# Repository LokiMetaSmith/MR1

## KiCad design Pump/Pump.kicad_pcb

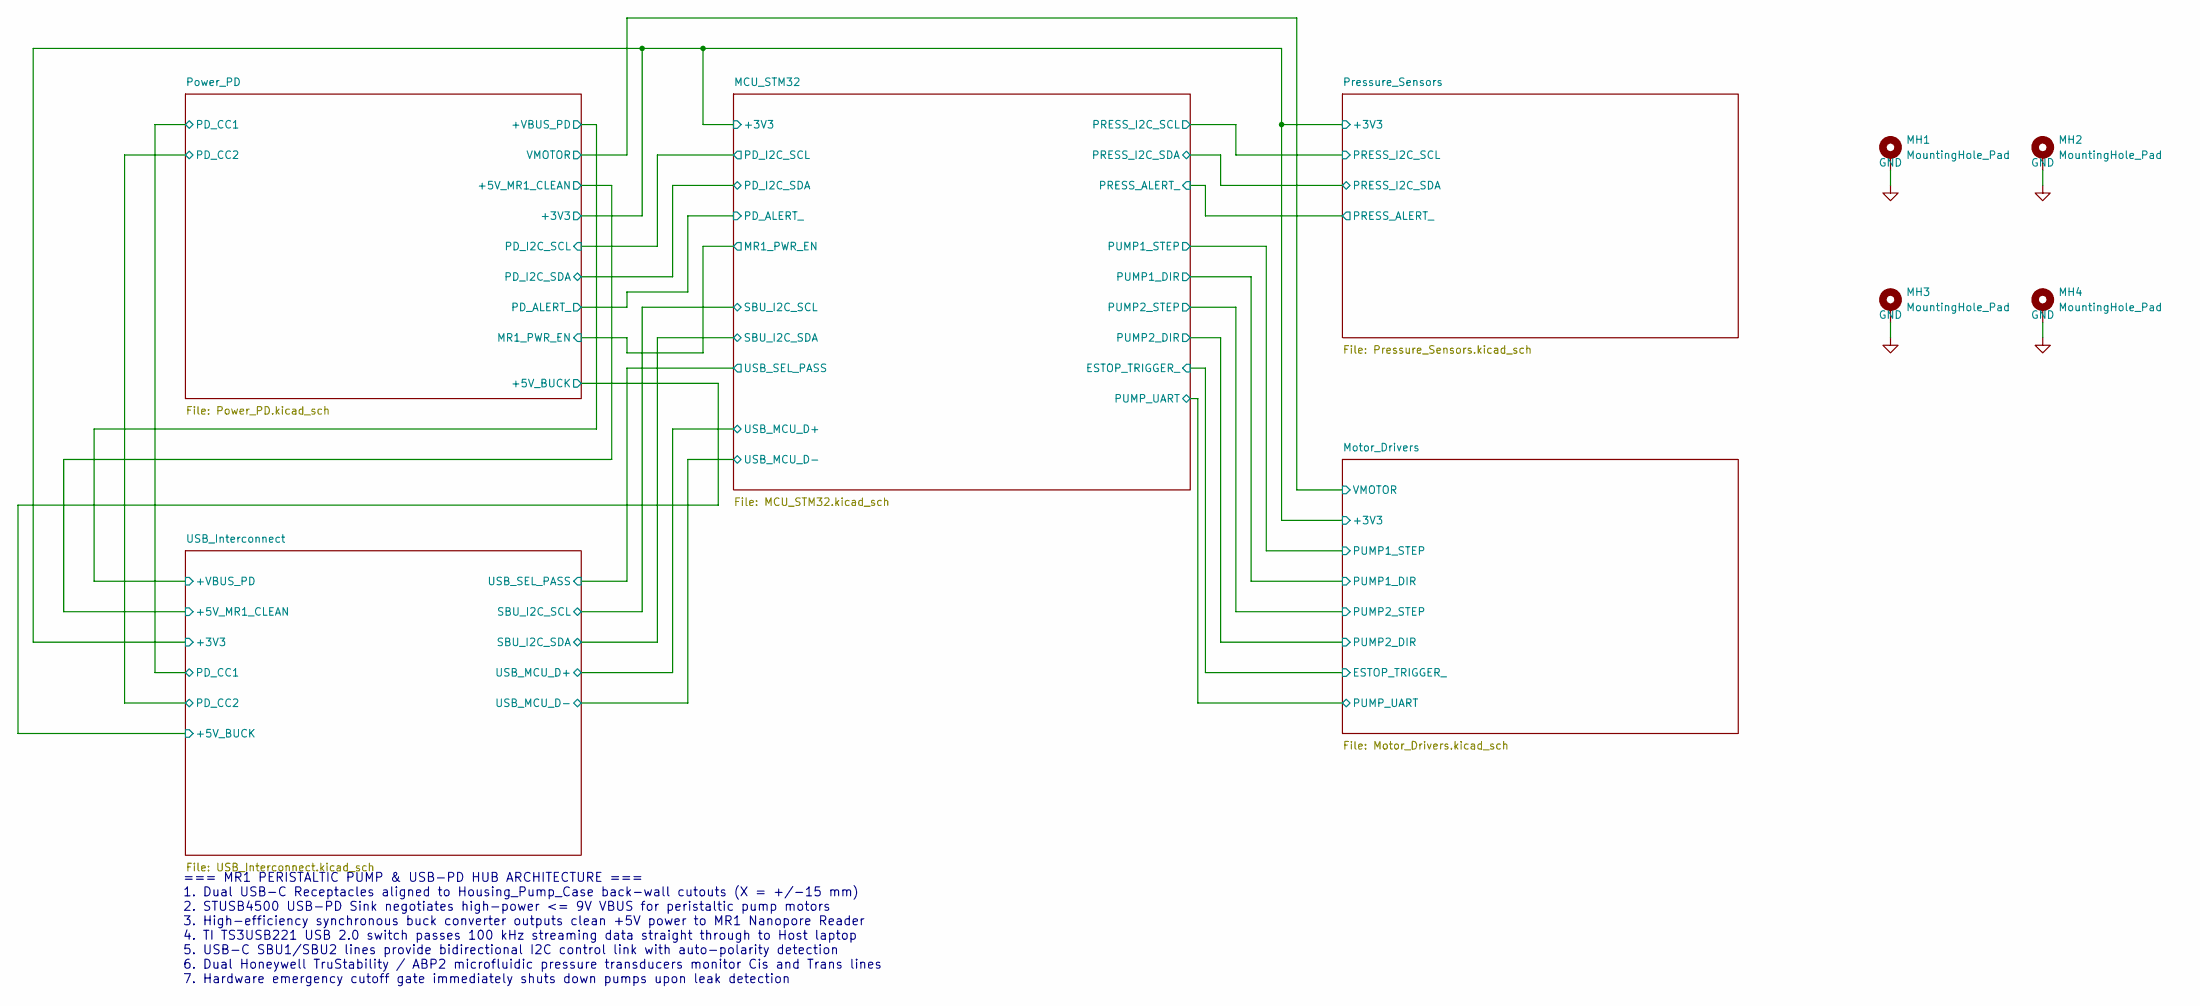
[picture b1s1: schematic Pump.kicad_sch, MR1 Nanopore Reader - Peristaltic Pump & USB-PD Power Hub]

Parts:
MH1, MH2, MH3, MH4: MountingHole_Pad; MountingHole_3.2mm_M3_Pad

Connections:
GND: MH1.1, MH2.1, MH3.1, MH4.1; also elsewhere on the board

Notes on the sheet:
=== MR1 PERISTALTIC PUMP & USB-PD HUB ARCHITECTURE === 1. Dual USB-C Receptacles aligned to Housing_Pump_Case back-wall cutouts (X = +/-15 mm) 2. STUSB4500 USB-PD Sink negotiates high-power <= 9V VBUS for peristaltic pump motors 3. High-efficiency synchronous buck converter outputs clean +5V power 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

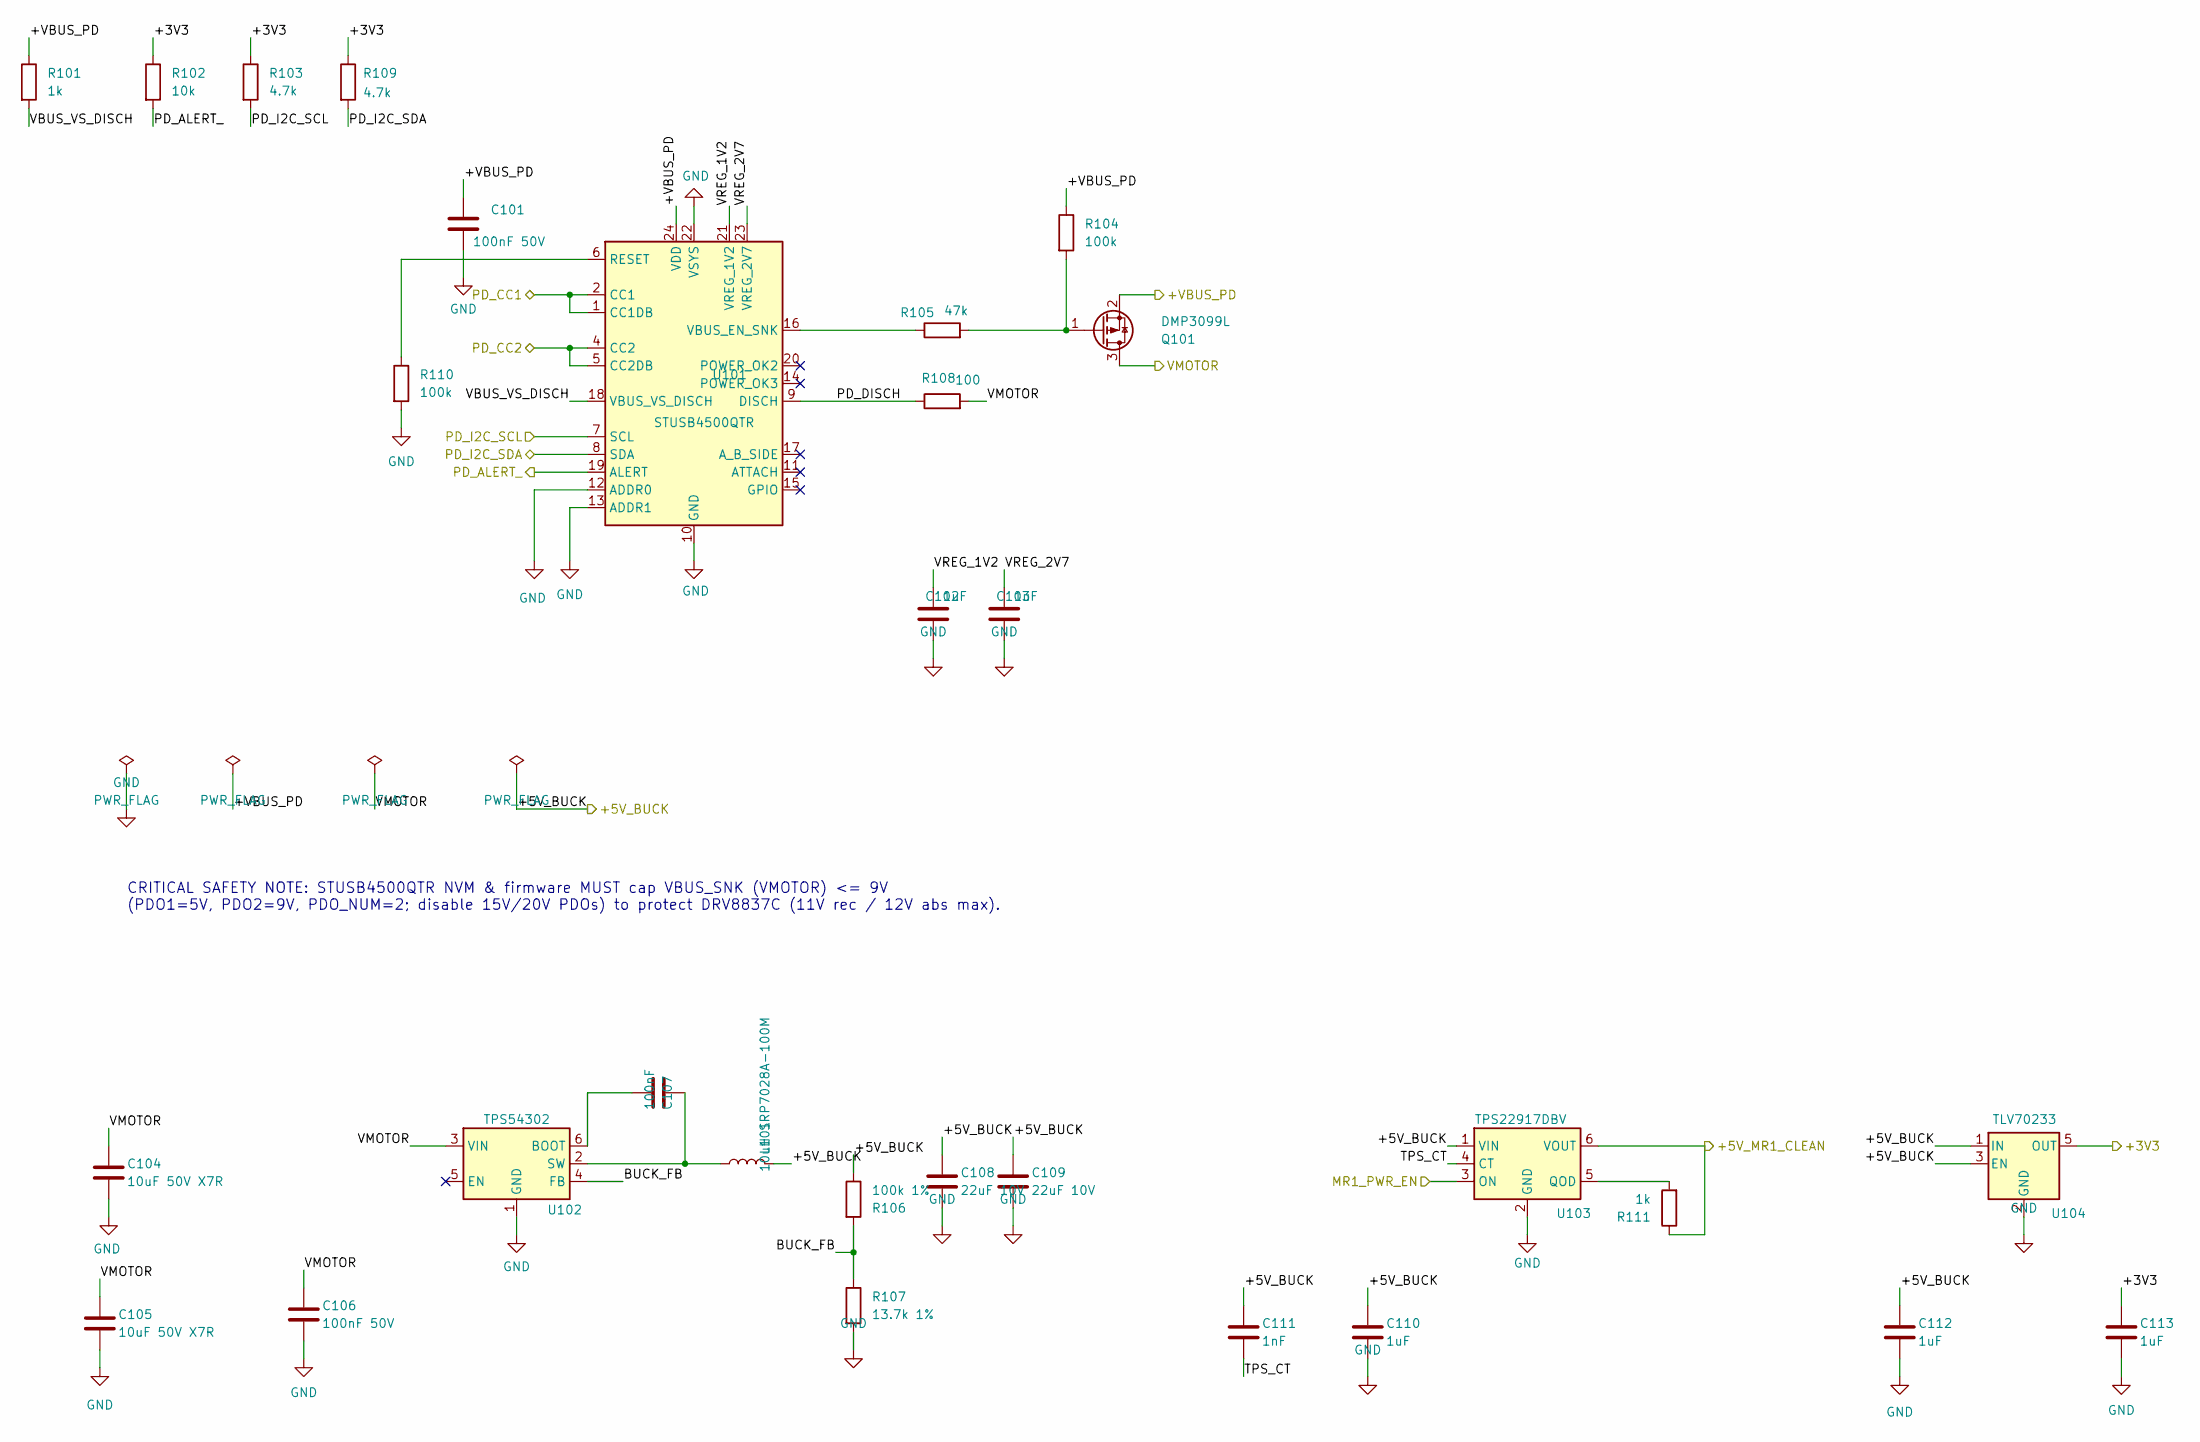
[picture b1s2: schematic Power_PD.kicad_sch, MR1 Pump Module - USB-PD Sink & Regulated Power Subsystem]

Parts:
C101, C106: 100nF 50V; C_0603_1608Metric; MPN CL10B104KB8NNNC; LCSC C1591
C102, C103, C110, C112, C113: 1uF; C_0402_1005Metric; MPN CL05A105KO5NNNC; LCSC C29266
C104, C105: 10uF 50V X7R; C_1206_3216Metric; MPN CL31B106KBHNNNE; LCSC C89632
C107: 100nF; C_0402_1005Metric; MPN CL05B104KO5NNNC; LCSC C1525
C108, C109: 22uF 10V; C_0805_2012Metric; MPN CL21A226MAQNNNE; LCSC C45783
C111: 1nF; C_0402_1005Metric; MPN 0402B102K500NT; LCSC C1523
L101: 10uH SRP7028A-100M; L_Bourns_SRP7028A_7.3x6.6mm; MPN SRP7028A-100M; LCSC C2687402
Q101: DMP3099L; SOT-23; MPN DMP3099L-7; LCSC C155244
R101, R111: 1k; R_0402_1005Metric; MPN 0402WGF1001TCE; LCSC C11702
R102: 10k; R_0402_1005Metric; MPN RC0402FR-0710KL; LCSC C60490
R103, R109: 4.7k; R_0402_1005Metric; MPN 0402WGF4701TCE; LCSC C25900
R104, R110: 100k; R_0402_1005Metric; MPN RC0402FR-07100KL; LCSC C60491
R105: 47k; R_0402_1005Metric; MPN 0402WGF4702TCE; LCSC C25792
R106: 100k 1%; R_0402_1005Metric; MPN RC0402FR-07100KL; LCSC C60491
R107: 13.7k 1%; R_0402_1005Metric; MPN RC0402FR-0713K7L; LCSC C274888
R108: 100; R_0402_1005Metric; MPN 0402WGF1000TCE; LCSC C25076
U101: STUSB4500QTR; QFN-24-1EP_4x4mm_P0.5mm_EP2.7x2.7mm; MPN STUSB4500QTR; LCSC C2678061
U102: TPS54302; SOT-23-6; MPN TPS54302DDCR; LCSC C311983
U103: TPS22917DBV; SOT-23-6; MPN TPS22917DBVR; LCSC C2681320
U104: TLV70233; SOT-23-5; MPN TLV70233DBVR; LCSC C26833

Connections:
/MCU_STM32/+3V3: C113.1, R102.1, R103.1, R109.1, U104.5 (OUT); also elsewhere on the board
/MCU_STM32/MR1_PWR_EN: U103.3 (ON); also elsewhere on the board
/Motor_Drivers/VMOTOR: C104.1, C105.1, C106.1, Q101.3 (D), R108.2, U102.3 (VIN); also elsewhere on the board
/Power_PD/+5V_BUCK: C108.1, C109.1, C110.1, C111.1, C112.1, L101.2, R106.1, U103.1 (VIN), U104.1 (IN), U104.3 (EN); also elsewhere on the board
/Power_PD/+VBUS_PD: C101.1, Q101.2 (S), R101.1, R104.1, U101.24 (VDD); also elsewhere on the board
/Power_PD/BUCK_FB: R106.2, R107.1, U102.4 (FB)
/Power_PD/PD_ALERT_: R102.2, U101.19 (ALERT); also elsewhere on the board
/Power_PD/PD_CC1: U101.1 (CC1DB), U101.2 (CC1); also elsewhere on the board
/Power_PD/PD_CC2: U101.4 (CC2), U101.5 (CC2DB); also elsewhere on the board
/Power_PD/PD_DISCH: R108.1, U101.9 (DISCH)
/Power_PD/PD_I2C_SCL: R103.2, U101.7 (SCL); also elsewhere on the board
/Power_PD/PD_I2C_SDA: R109.2, U101.8 (SDA); also elsewhere on the board
/Power_PD/TPS_CT: C111.2, U103.4 (CT)
/Power_PD/VBUS_VS_DISCH: R101.2, U101.18 (VBUS_VS_DISCH)
/Power_PD/VREG_1V2: C102.1, U101.21 (VREG_1V2)
/Power_PD/VREG_2V7: C103.1, U101.23 (VREG_2V7)
/USB_Interconnect/+5V_MR1_CLEAN: R111.1, U103.6 (VOUT); also elsewhere on the board
GND: C101.2, C102.2, C103.2, C104.2, C105.2, C106.2, C108.2, C109.2, C110.2, C112.2, C113.2, R107.2, R110.2, U101.10 (GND), U101.12 (ADDR0), U101.13 (ADDR1), U101.22 (VSYS), U101.25 (GND), U102.1 (GND), U103.2 (GND), U104.2 (GND); also elsewhere on the board
unnamed: Q101.1 (G), R104.2, R105.2
unnamed: R110.1, U101.6 (RESET)
unnamed: R105.1, U101.16 (VBUS_EN_SNK)
unnamed: C107.1, U102.6 (BOOT)
unnamed: C107.2, L101.1, U102.2 (SW)
unnamed: R111.2, U103.5 (QOD)

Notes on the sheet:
CRITICAL SAFETY NOTE: STUSB4500QTR NVM & firmware MUST cap VBUS_SNK (VMOTOR) <= 9V (PDO1=5V, PDO2=9V, PDO_NUM=2; disable 15V/20V PDOs) to protect DRV8837C (11V rec / 12V abs max).

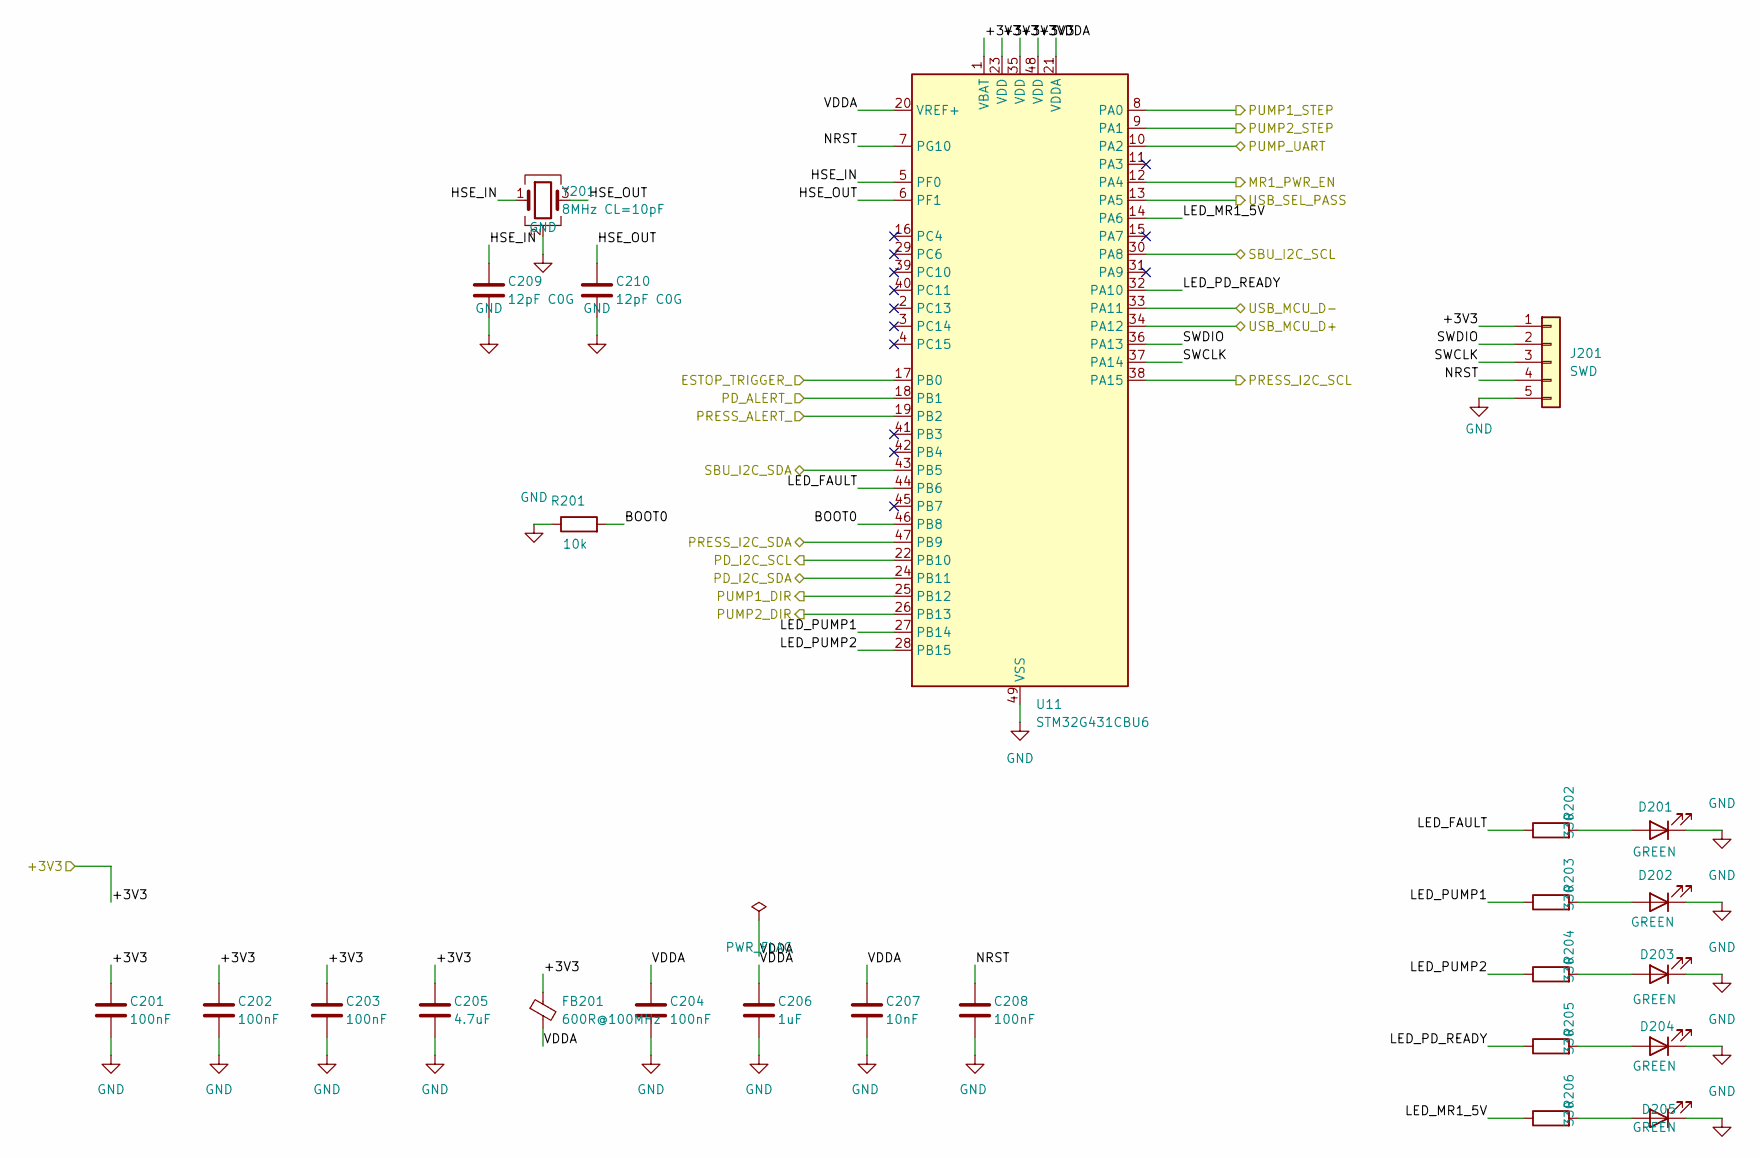
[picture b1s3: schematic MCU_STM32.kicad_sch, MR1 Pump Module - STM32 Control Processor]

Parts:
C201, C202, C203, C204, C208: 100nF; C_0402_1005Metric; MPN CL05B104KO5NNNC; LCSC C1525
C205: 4.7uF; C_0603_1608Metric; MPN CL10A475KP8NNNC; LCSC C1705
C206: 1uF; C_0402_1005Metric; MPN CL05A105KO5NNNC; LCSC C29266
C207: 10nF; C_0402_1005Metric; MPN CL05B103KB5NNNC; LCSC C15195
C209, C210: 12pF C0G; C_0402_1005Metric; MPN 0402CG120J500NT; LCSC C1547
D201, D202, D203, D204, D205: GREEN; LED_0603_1608Metric; MPN KT-0603G; LCSC C12624
FB201: 600R@100MHz; L_0603_1608Metric; MPN CBW160808U601T; LCSC C139183
J201: SWD; PinHeader_1x05_P2.54mm_Vertical; MPN PZ254V-11-05P; LCSC C492404
R201: 10k; R_0402_1005Metric; MPN RC0402FR-0710KL; LCSC C60490
R202, R203, R204, R205, R206: 330; R_0402_1005Metric; MPN 0402WGF3300TCE; LCSC C25104
U11: STM32G431CBU6; QFN-48-1EP_7x7mm_P0.5mm_EP5.6x5.6mm; MPN STM32G431CBU6; LCSC C529356
Y201: 8MHz CL=10pF; Crystal_SMD_3225-4Pin_3.2x2.5mm; MPN 3225-8.00-10-10-10/A; LCSC C518154

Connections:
/MCU_STM32/+3V3: C201.1, C202.1, C203.1, C205.1, FB201.1, J201.1, U11.1 (VBAT), U11.23 (VDD), U11.35 (VDD), U11.48 (VDD); also elsewhere on the board
/MCU_STM32/BOOT0: R201.2, U11.46 (PB8)
/MCU_STM32/ESTOP_TRIGGER_: U11.17 (PB0); also elsewhere on the board
/MCU_STM32/HSE_IN: C209.1, U11.5 (PF0), Y201.1
/MCU_STM32/HSE_OUT: C210.1, U11.6 (PF1), Y201.3
/MCU_STM32/LED_FAULT: R202.1, U11.44 (PB6)
/MCU_STM32/LED_MR1_5V: R206.1, U11.14 (PA6)
/MCU_STM32/LED_PD_READY: R205.1, U11.32 (PA10)
/MCU_STM32/LED_PUMP1: R203.1, U11.27 (PB14)
/MCU_STM32/LED_PUMP2: R204.1, U11.28 (PB15)
/MCU_STM32/MR1_PWR_EN: U11.12 (PA4); also elsewhere on the board
/MCU_STM32/NRST: C208.1, J201.4, U11.7 (PG10)
/MCU_STM32/PRESS_ALERT_: U11.19 (PB2); also elsewhere on the board
/MCU_STM32/PUMP1_DIR: U11.25 (PB12); also elsewhere on the board
/MCU_STM32/PUMP1_STEP: U11.8 (PA0); also elsewhere on the board
/MCU_STM32/PUMP2_DIR: U11.26 (PB13); also elsewhere on the board
/MCU_STM32/PUMP2_STEP: U11.9 (PA1); also elsewhere on the board
/MCU_STM32/PUMP_UART: U11.10 (PA2); also elsewhere on the board
/MCU_STM32/SWCLK: J201.3, U11.37 (PA14)
/MCU_STM32/SWDIO: J201.2, U11.36 (PA13)
/MCU_STM32/USB_MCU_D+: U11.34 (PA12); also elsewhere on the board
/MCU_STM32/USB_MCU_D-: U11.33 (PA11); also elsewhere on the board
/MCU_STM32/USB_SEL_PASS: U11.13 (PA5); also elsewhere on the board
/MCU_STM32/VDDA: C204.1, C206.1, C207.1, FB201.2, U11.20 (VREF+), U11.21 (VDDA)
/Power_PD/PD_ALERT_: U11.18 (PB1); also elsewhere on the board
/Power_PD/PD_I2C_SCL: U11.22 (PB10); also elsewhere on the board
/Power_PD/PD_I2C_SDA: U11.24 (PB11); also elsewhere on the board
/Pressure_Sensors/PRESS_I2C_SCL: U11.38 (PA15); also elsewhere on the board
/Pressure_Sensors/PRESS_I2C_SDA: U11.47 (PB9); also elsewhere on the board
/USB_Interconnect/SBU_I2C_SCL: U11.30 (PA8); also elsewhere on the board
/USB_Interconnect/SBU_I2C_SDA: U11.43 (PB5); also elsewhere on the board
GND: C201.2, C202.2, C203.2, C204.2, C205.2, C206.2, C207.2, C208.2, C209.2, C210.2, D201.1 (K), D202.1 (K), D203.1 (K), D204.1 (K), D205.1 (K), J201.5, R201.1, U11.49 (VSS), Y201.2 (G), Y201.4 (G); also elsewhere on the board
unnamed: D201.2 (A), R202.2
unnamed: D202.2 (A), R203.2
unnamed: D203.2 (A), R204.2
unnamed: D204.2 (A), R205.2
unnamed: D205.2 (A), R206.2

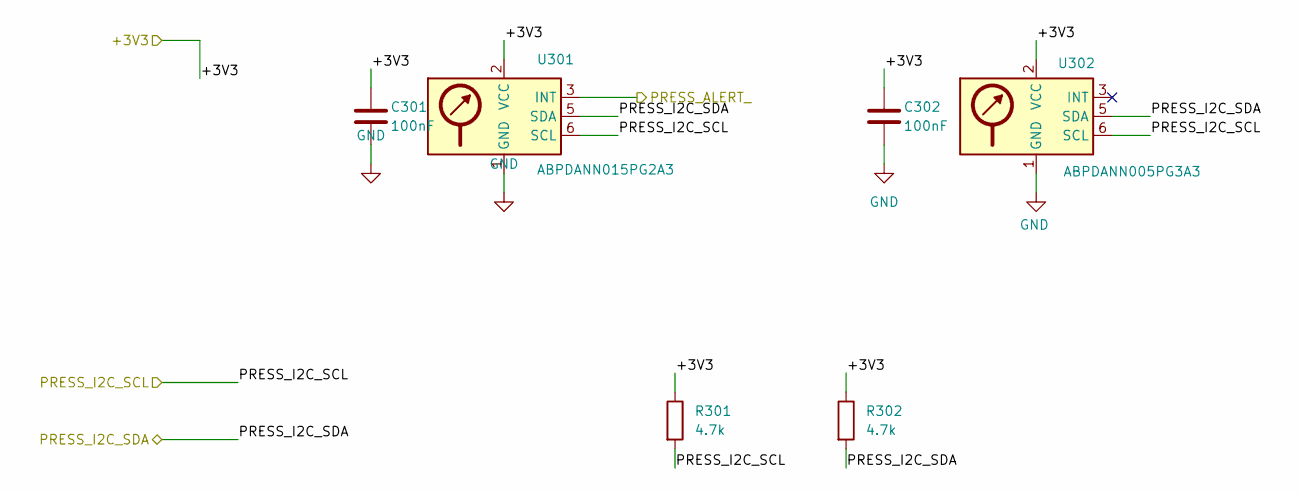
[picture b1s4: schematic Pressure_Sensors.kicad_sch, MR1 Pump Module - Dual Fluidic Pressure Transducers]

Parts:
C301, C302: 100nF; C_0402_1005Metric; MPN CL05B104KO5NNNC; LCSC C1525
R301, R302: 4.7k; R_0402_1005Metric; MPN 0402WGF4701TCE; LCSC C25900
U301: ABPDANN015PG2A3; Honeywell_ABPDAN; MPN ABPDANN015PG2A3; LCSC ABPDANN015PG2A3
U302: ABPDANN005PG3A3; Honeywell_ABPDAN; MPN ABPDANN005PG3A3; LCSC ABPDANN005PG3A3

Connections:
/MCU_STM32/+3V3: C301.1, C302.1, R301.1, R302.1, U301.2 (VCC), U302.2 (VCC); also elsewhere on the board
/MCU_STM32/PRESS_ALERT_: U301.3 (INT); also elsewhere on the board
/Pressure_Sensors/PRESS_I2C_SCL: R301.2, U301.6 (SCL), U302.6 (SCL); also elsewhere on the board
/Pressure_Sensors/PRESS_I2C_SDA: R302.2, U301.5 (SDA), U302.5 (SDA); also elsewhere on the board
GND: C301.2, C302.2, U301.1 (GND), U302.1 (GND); also elsewhere on the board

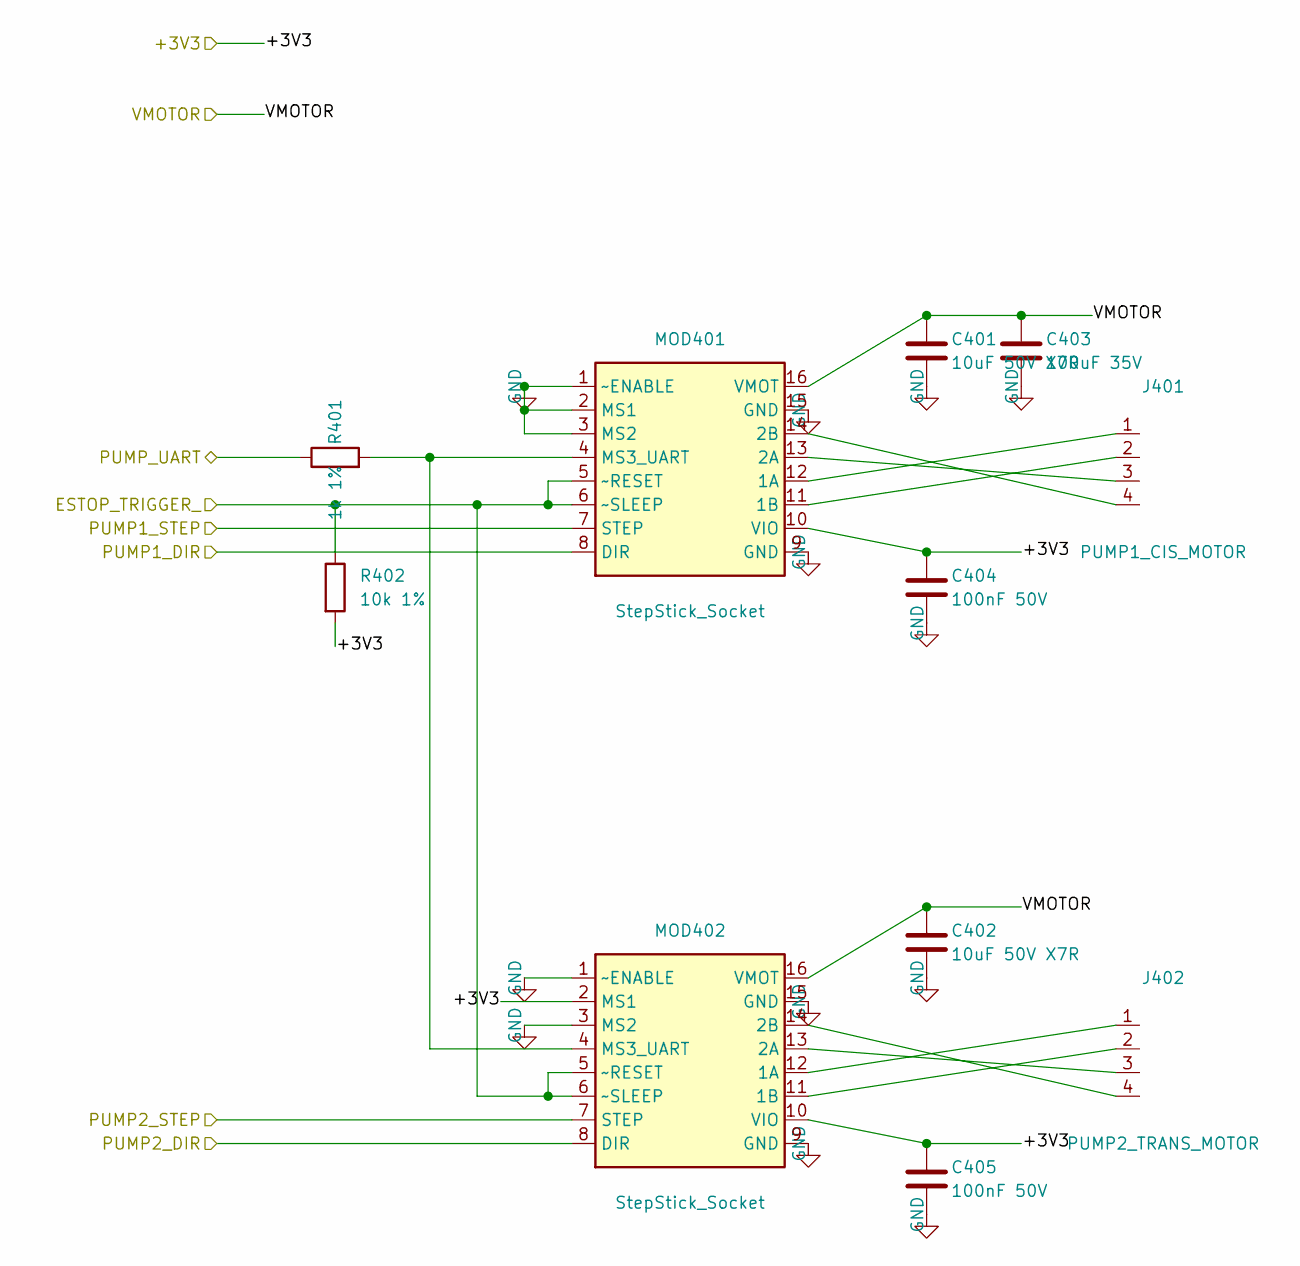
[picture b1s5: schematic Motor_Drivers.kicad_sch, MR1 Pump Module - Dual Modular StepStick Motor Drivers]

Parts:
C401, C402: 10uF 50V X7R; C_1206_3216Metric; MPN CL31B106KBHNNNE; LCSC C89632
C403: 100uF 35V; CP_Elec_6.3x7.7; MPN VT1V101M0607; LCSC C134544
C404, C405: 100nF 50V; C_0402_1005Metric; MPN CL05B104KO5NNNC; LCSC C1525
J401: PUMP1_CIS_MOTOR; JST_XH_B4B-XH-A_1x04_P2.50mm_Vertical; MPN B4B-XH-A(LF)(SN); LCSC C144395
J402: PUMP2_TRANS_MOTOR; JST_XH_B4B-XH-A_1x04_P2.50mm_Vertical; MPN B4B-XH-A(LF)(SN); LCSC C144395
MOD401, MOD402: StepStick_Socket; Pololu_Breakout-16_15.2x20.3mm; MPN PinHeader_1x08_P2.54mm_Female; LCSC C22550
R401: 1k 1%; R_0402_1005Metric; MPN 0402WGF1001TCE; LCSC C11702
R402: 10k 1%; R_0402_1005Metric; MPN 0402WGF1002TCE; LCSC C25744

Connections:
/MCU_STM32/+3V3: C404.1, C405.1, MOD401.10 (VIO), MOD402.2 (MS1), MOD402.10 (VIO), R402.2; also elsewhere on the board
/MCU_STM32/ESTOP_TRIGGER_: MOD401.5 (~RESET), MOD401.6 (~SLEEP), MOD402.5 (~RESET), MOD402.6 (~SLEEP), R402.1; also elsewhere on the board
/MCU_STM32/PUMP1_DIR: MOD401.8 (DIR); also elsewhere on the board
/MCU_STM32/PUMP1_STEP: MOD401.7 (STEP); also elsewhere on the board
/MCU_STM32/PUMP2_DIR: MOD402.8 (DIR); also elsewhere on the board
/MCU_STM32/PUMP2_STEP: MOD402.7 (STEP); also elsewhere on the board
/MCU_STM32/PUMP_UART: R401.1; also elsewhere on the board
/Motor_Drivers/VMOTOR: C401.1, C402.1, C403.1, MOD401.16 (VMOT), MOD402.16 (VMOT); also elsewhere on the board
GND: C401.2, C402.2, C403.2, C404.2, C405.2, MOD401.1 (~ENABLE), MOD401.2 (MS1), MOD401.3 (MS2), MOD401.9 (GND), MOD401.15 (GND), MOD402.1 (~ENABLE), MOD402.3 (MS2), MOD402.9 (GND), MOD402.15 (GND); also elsewhere on the board
unnamed: J401.1, MOD401.12 (1A)
unnamed: J401.2, MOD401.11 (1B)
unnamed: J401.3, MOD401.13 (2A)
unnamed: J401.4, MOD401.14 (2B)
unnamed: J402.1, MOD402.12 (1A)
unnamed: J402.2, MOD402.11 (1B)
unnamed: J402.3, MOD402.13 (2A)
unnamed: J402.4, MOD402.14 (2B)
unnamed: MOD401.4 (MS3_UART), MOD402.4 (MS3_UART), R401.2

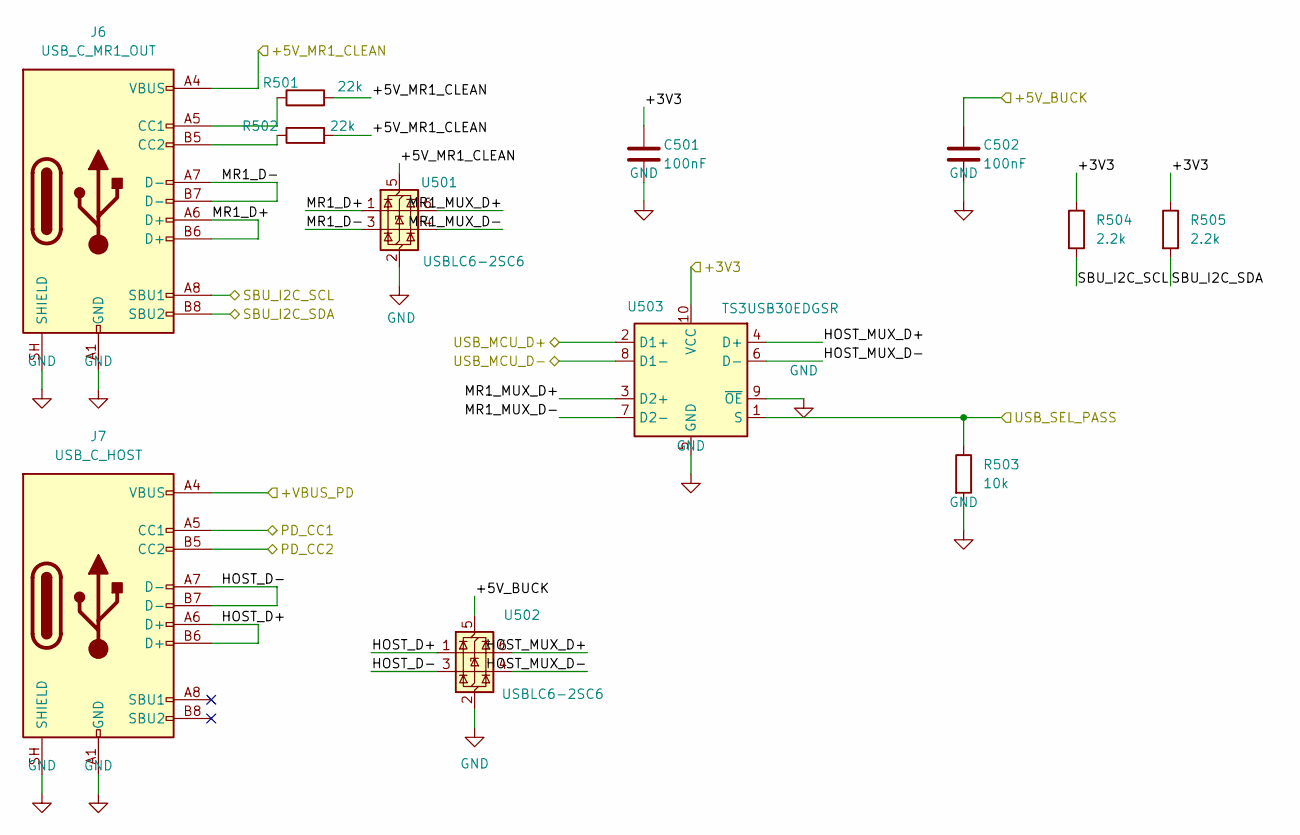
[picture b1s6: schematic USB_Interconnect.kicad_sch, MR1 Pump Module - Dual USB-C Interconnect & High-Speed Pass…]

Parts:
C501, C502: 100nF; C_0402_1005Metric; MPN CL05B104KO5NNNC; LCSC C1525
J6: USB_C_MR1_OUT; USB_C_Receptacle_GCT_USB4085; MPN USB4085-GF-A; LCSC C7095263
J7: USB_C_HOST; USB_C_Receptacle_GCT_USB4085; MPN USB4085-GF-A; LCSC C7095263
R501, R502: 22k; R_0402_1005Metric; MPN 0402WGF2202TCE; LCSC C25768
R503: 10k; R_0402_1005Metric; MPN RC0402FR-0710KL; LCSC C60490
R504, R505: 2.2k; R_0402_1005Metric; MPN 0402WGF2201TCE; LCSC C25879
U501, U502: USBLC6-2SC6; SOT-23-6; MPN USBLC6-2SC6; LCSC C7519
U503: TS3USB30EDGSR; TSSOP-10_3x3mm_P0.5mm; MPN TS3USB30EDGSR; LCSC C131998

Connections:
/MCU_STM32/+3V3: C501.1, R504.1, R505.1, U503.10 (VCC); also elsewhere on the board
/MCU_STM32/USB_MCU_D+: U503.2 (D1+); also elsewhere on the board
/MCU_STM32/USB_MCU_D-: U503.8 (D1-); also elsewhere on the board
/MCU_STM32/USB_SEL_PASS: R503.1, U503.1 (S); also elsewhere on the board
/Power_PD/+5V_BUCK: C502.1, U502.5 (VBUS); also elsewhere on the board
/Power_PD/+VBUS_PD: J7.A4 (VBUS), J7.A9 (VBUS), J7.B4 (VBUS), J7.B9 (VBUS); also elsewhere on the board
/Power_PD/PD_CC1: J7.A5 (CC1); also elsewhere on the board
/Power_PD/PD_CC2: J7.B5 (CC2); also elsewhere on the board
/USB_Interconnect/+5V_MR1_CLEAN: J6.A4 (VBUS), J6.A9 (VBUS), J6.B4 (VBUS), J6.B9 (VBUS), R501.2, R502.2, U501.5 (VBUS); also elsewhere on the board
/USB_Interconnect/HOST_D+: J7.A6 (D+), J7.B6 (D+), U502.1 (I/O1)
/USB_Interconnect/HOST_D-: J7.A7 (D-), J7.B7 (D-), U502.3 (I/O2)
/USB_Interconnect/HOST_MUX_D+: U502.6 (I/O1), U503.4 (D+)
/USB_Interconnect/HOST_MUX_D-: U502.4 (I/O2), U503.6 (D-)
/USB_Interconnect/MR1_D+: J6.A6 (D+), J6.B6 (D+), U501.1 (I/O1)
/USB_Interconnect/MR1_D-: J6.A7 (D-), J6.B7 (D-), U501.3 (I/O2)
/USB_Interconnect/MR1_MUX_D+: U501.6 (I/O1), U503.3 (D2+)
/USB_Interconnect/MR1_MUX_D-: U501.4 (I/O2), U503.7 (D2-)
/USB_Interconnect/SBU_I2C_SCL: J6.A8 (SBU1), R504.2; also elsewhere on the board
/USB_Interconnect/SBU_I2C_SDA: J6.B8 (SBU2), R505.2; also elsewhere on the board
GND: C501.2, C502.2, J6.A1 (GND), J6.A12 (GND), J6.B1 (GND), J6.B12 (GND), J6.SH (SHIELD), J7.A1 (GND), J7.A12 (GND), J7.B1 (GND), J7.B12 (GND), J7.SH (SHIELD), R503.2, U501.2 (GND), U502.2 (GND), U503.5 (GND), U503.9 (~OE); also elsewhere on the board
unnamed: J6.A5 (CC1), R501.1
unnamed: J6.B5 (CC2), R502.1

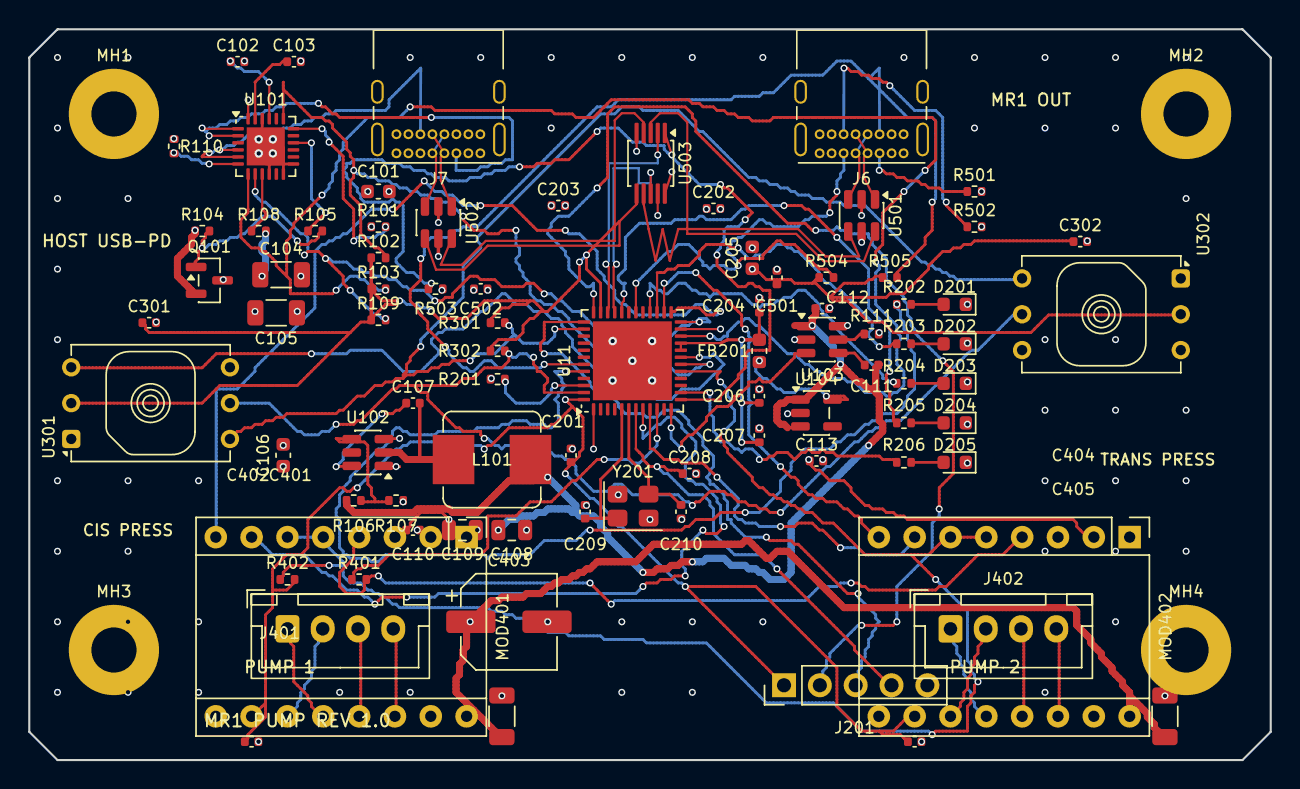
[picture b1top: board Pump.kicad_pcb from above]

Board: 4 copper layers, 88.0 x 51.8 mm, 88 parts (0 on the bottom side), 74 nets.

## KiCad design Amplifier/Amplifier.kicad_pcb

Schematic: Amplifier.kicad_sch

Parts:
C1: 2pF; C_0402_1005Metric; LCSC C161316
C3: 15pF; C_0402_1005Metric; LCSC C33148
C6, C9, C14, C20: 100nF; C_0402_1005Metric; LCSC C49678
C7, C8: 10nF; C_0402_1005Metric; LCSC C1525
C10, C12, C19, C31, C32, C33, C34, C39: 100nF; C_0402_1005Metric; LCSC C15255
C11: 4.7u; C_0402_1005Metric; Manufacturer_Part_Number JMK107C6475KA-T; LCSC C19702
C29, C30: 10pF; C_0402_1005Metric; LCSC C1548
C35: 10u; C_0402_1005Metric; MPN GRM21BR61H106KE43K; LCSC C1713
C40, C42: 100nF; C_0402_1005Metric; Mouser PN 710-885012205037; LCSC C15255
C41: 1nF; C_0402_1005Metric; LCSC C1523
D82: MBR0540; D_SOD-123; MPN MBR0540L-TP; LCSC C5204747
FB1, FB2: HZ0402A152R-10; L_0402_1005Metric; LCSC C442654
J7: Conn_01x14_MountingPin; XUNPU_FPC-05F-14PH15_1x14_P0.5mm_Horizontal; LCSC C2856818
NT3, NT4, NT6, NT7, NT8, NT9: NetTie_2; NetTie-2_SMD_Pad0.5mm
P1, P3, P4, P6, P7, P8, P9, P10, P11, P12: PogoPin_MillMax_SMT_1Pin
P2, P5: PogoPin_MillMax_SMT_1Pin_Guarded; PogoPin_SMT_Circle_Guard_Notched
Q3: 2N7002; SOT-23; LCSC C8545
R1: 1G; R_0402_1005Metric; LCSC HVC0805T1007JET
R3, R5: 1K; R_0402_1005Metric; LCSC C17513
R4: 100; R_0402_1005Metric; LCSC C25097
R6: 1K; R_0402_1005Metric; LCSC C25149
R8: 100; R_0402_1005Metric; LCSC C17408
R10, R14, R15: 100k; R_0402_1005Metric; LCSC C60491
R16: 1M; R_0402_1005Metric; LCSC C25488
R27, R41: 27; R_0402_1005Metric; MPN RC0402JR-0727RL; LCSC C25078
R28, R29, R30, R31, R32, R33: 49.9; R_0402_1005Metric; MPN RC0402JR-0727RL; LCSC C4074199
R43, R44, R45, R46: 499 (0.1%); R_0402_1005Metric; LCSC C25132
SYM1: SYM_Arrow45_Large; Fluid_Overlay_SILKSCREEN_ONLY
U2: LMP7721; SOIC-8_3.9x4.9mm_P1.27mm; Mouser PN 926-LMP7721MA/NOPB
U5: OPA2192IDR; SOIC-8_3.9x4.9mm_P1.27mm; MPN OPA2192IDR; LCSC C110074
U6: ADA4940-1xCP; LFCSP-16-1EP_3x3mm_P0.5mm_EP1.3x1.3mm_ThermalVias; MPN ADA4940-1ACPZ-RL; LCSC C529241
U13: AD40xxBRMZ; MSOP-10_3x3mm_P0.5mm; MPN AD4011BCPZ-RL7; LCSC C539308
U14: LP5907MFX-1.8; SOT-23-5; MPN LP5907MFX-1.8/NOPB; LCSC C92498
U16: LTC6268xS8; SO-8_3.9x4.9mm_P1.27mm; MPN LTC6268IS8#TRPBF; LCSC C689169
U17: ADG1219BRMZ; MSOP-8_3x3mm_P0.65mm; MPN ADG1219BRMZ; LCSC C206796

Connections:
+1V8: C11.1, U13.2 (VDD), U14.5 (OUT)
+3.3VA: C33.1, FB1.2, FB2.1, R14.1, U13.10 (VIO), U17.1 (EN)
+3V3: FB1.1, J7.1
/>PORE_AMP: J7.14, P9.1 (PIN_1)
/CE_GNDA: NT8.1, P7.1 (PIN_1)
/GDAC_CLK: R31.1, U13.8 (SCK)
/GDAC_EN: R29.1, U13.6 (CNV)
/GDAC_SDI: R30.1, U13.9 (SDI)
/GDAC_SDO: R28.1, U13.7 (SDO)
/GNDA_SHLD: NT9.2, P1.1 (PIN_1)
/GNDA_WEEP: D82.2 (A), NT6.1, P12.1 (PIN_1), Q3.2 (S)
/GUARD: NT3.1, P4.1 (PIN_1), P5.2 (GUARD), P6.1 (PIN_1), U2.2 (NC), U2.7 (NC)
/GUARD_WIDE: P2.2 (GUARD), P3.1 (PIN_1), U5.6 (-), U5.7
/RE_TRANS: P8.1 (PIN_1), R6.2
/ROUTE_SEL: R33.1, U17.8 (IN)
/R_WEEP_GATE: D82.1 (K), R15.2, R16.1
/R_WEEP_PULL: Q3.3 (D), R14.2, U14.3 (EN)
/Route1_OUT: C9.1, R3.1, U16.6, U17.7 (SA)
/Route2_OUT: R32.2, U17.5 (SB)
/SHIELD: NT4.1, NT7.2
/SHIELD_AMP: J7.MP (MountPin), NT4.2, NT9.1
/Signal_Return: R45.1, U17.6 (D)
/Vbias: C6.1, C14.1, C35.1, NT3.2, R4.1, R6.1, U2.1 (+), U5.3 (+), U5.5 (+), U13.1 (REF), U16.1 (NC), U16.4 (NC)
/Virtual_Ground: C9.2, R3.2, R4.2, U16.2 (-)
/WEEP_SENSE: P11.1 (PIN_1), R15.1
/WS_CIS: C1.2, P5.1 (SIG), R1.2, U2.8 (-)
/WS_CIS_WIDE: C3.2, P2.1 (SIG), R10.2, U5.2 (-)
GND: J7.2, J7.8
GNDA: C6.2, C7.2, C8.2, C10.2, C11.2, C12.2, C14.2, C19.2, C20.2, C29.1, C30.2, C31.2, C32.2, C33.2, C34.2, C35.2, C39.2, C40.2, C42.2, J7.9, J7.11, J7.13, NT6.2, NT8.2, P10.1 (PIN_1), R5.2, R43.1, U6.9 (VOCM), U6.17 (EP), U13.5 (GND), U14.2 (GND), U17.3 (GND)
unnamed: C1.1, R1.1, R8.2, U2.4
unnamed: C39.1, NT7.1
unnamed: J7.3, R31.2
unnamed: J7.4, R33.2
unnamed: J7.5, R28.2
unnamed: J7.6, R29.2
unnamed: J7.7, R30.2
unnamed: Q3.1 (G), R16.2
unnamed: C3.1, R10.1, R32.1, U5.1
unnamed: R44.2, U6.4 (+FB)
unnamed: R45.2, R46.2, U6.2 (+IN)
unnamed: R27.1, U6.10 (+OUT)
unnamed: R46.1, U6.1 (-FB)
unnamed: R43.2, R44.1, U6.3 (-IN)
unnamed: R41.1, U6.11 (-OUT)
unnamed: C29.2, C41.1, R27.2, U13.3 (IN+)
unnamed: C30.1, C41.2, R41.2, U13.4 (IN-)
unnamed: C34.1, FB2.2, U14.1 (IN)
unnamed: R5.1, R8.1, U16.3 (+)
VDDA: C7.1, C10.1, C19.1, C31.1, C40.1, J7.10, U2.6 (V+), U5.8 (V+), U6.5 (+Vs), U6.6 (+Vs), U6.7 (+Vs), U6.8 (+Vs), U16.7 (V+), U17.2 (VDD)
VSSA: C8.1, C12.1, C20.1, C32.1, C42.1, J7.12, U2.3 (V-), U5.4 (V-), U6.13 (-Vs), U6.14 (-Vs), U6.15 (-Vs), U6.16 (-Vs), U16.5 (V-), U17.4 (VSS)

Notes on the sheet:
SM10B-SRSS-TB
3. Selecting the Precision ADC To capture <1µV signals, you need a 24-bit or 32-bit Delta-Sigma ADC. The standard 12-bit or 16-bit SAR ADCs used in microcontrollers will not see the signal floor you have created. Top Recommendations: TI ADS1261 (24-bit / 32-bit mode): Why: It has a built-in PGA (Pr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
Ceramic capacitors are piezoelectric – mechanical vibrations and noises will create charge across the capacitor. Be careful when using ceramic caps in the input, integration, feedback or biasing networks.
LTC6268
consider cat 7 flat ribbon cable, 8 pairs, shielded
low noise voltage converters
Stage 2 Voltage Amplifier
R1 1206
Stage 1: Transimpedance Amp
Stability in ultra-low noise regulators is dictated by the **Output Capacitance ()** and the **Noise Reduction Capacitance ()**. If these ratios are wrong, the LDO will oscillate, turning your "clean" power supply into a radio transmitter. ### 1. The LDO Component Values (The Critical Stage) These 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
https://www.vpi.us/bulk-cable-sf/super-flat-cat7-736#idTab9
R_DAMP
MG Chemicals 422C conformal coating
amplifier board
RF-damping capacitor
For high-speed nanopore sensing, the answer is definitive: **Do NOT tie them together.** You should use **Separate Voltage References** (or at least strictly buffered separate paths) for your ADC and your Bias Driver. Here is the engineering reality of why sharing a "Reference Rail" will introduce 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
No, the schematic recipe I provided above is **Fixed Gain (10x)**. It uses a standard resistor, so the zoom level is locked. Since you are removing the MAX9939 (which *was* a variable gain amplifier), you likely want to keep that functionality—especially since Nanopores vary wildly in current. A 1 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
PTFE (ZYF255DA): Dk .approx 2.55
499Ω Metal Film Resistor
we need to play back a waveform
250ft 32AWG CAT7 STP Solid, 0.075" Super Flat Bulk Ethernet Bare Copper Cable - White.
Using an **Optically Isolated Current Source (LED + Photodiode)** is the "Ferrari" of dummy loads for nanopore amplifiers. While the resistor method (like in the EarlGrey PDF) is great for checking baseline noise, the LED/Photodiode method is superior for checking **bandwidth** and **step response*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
pins for holding the board in place while applying adhesive https://www.mcmaster.com/98378A208/
SSH-003T-P0.2-H #32 to #28 (0.032 to 0.081) 0.4 to 0.8 23,000
SHR-10V-S
C2 and C3 X5R

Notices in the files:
tests/test_interposer_kicad.py:
Dedicated to the public domain under CC0 1.0 Universal (CC0-1.0).
SPDX-License-Identifier: CC0-1.0
